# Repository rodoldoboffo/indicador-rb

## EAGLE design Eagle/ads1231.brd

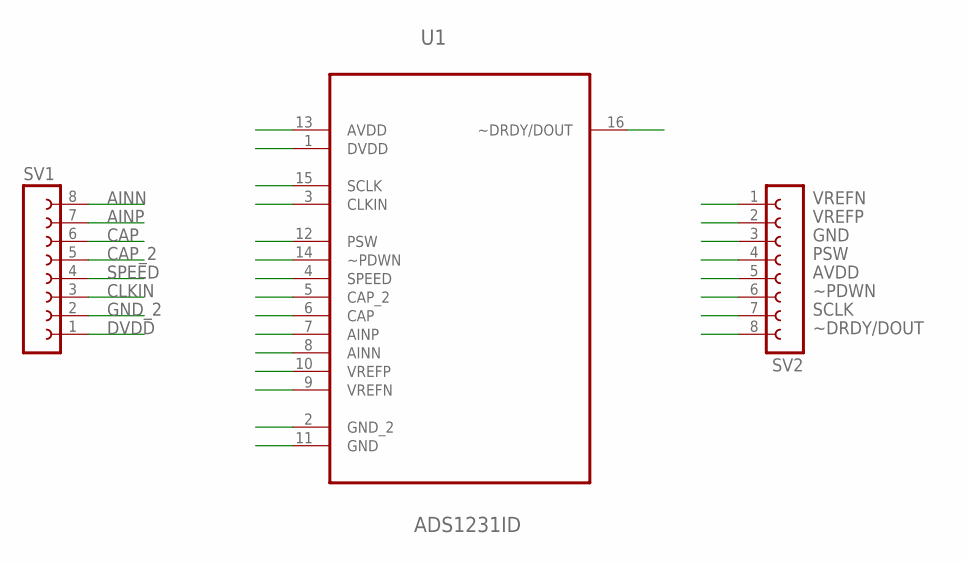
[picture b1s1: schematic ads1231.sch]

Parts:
SV1, SV2: FE08-1; FE08
U1: ADS1231ID; SOIC127P600X175-16N

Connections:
AINN: SV1.8, U1.8 (AINN)
AINP: SV1.7, U1.7 (AINP)
AVDD: SV2.5, U1.13 (AVDD)
CAP: SV1.6, U1.6 (CAP)
CAP_2: SV1.5, U1.5 (CAP_2)
CLKIN: SV1.3, U1.3 (CLKIN)
DVDD: SV1.1, U1.1 (DVDD)
GND: SV2.3, U1.11 (GND)
GND_2: SV1.2, U1.2 (GND_2)
PSW: SV2.4, U1.12 (PSW)
SCLK: SV2.7, U1.15 (SCLK)
SPEED: SV1.4, U1.4 (SPEED)
VREFN: SV2.1, U1.9 (VREFN)
VREFP: SV2.2, U1.10 (VREFP)
~DRDY/DOUT: SV2.8, U1.16 (~DRDY/DOUT)
~PDWN: SV2.6, U1.14 (~PDWN)

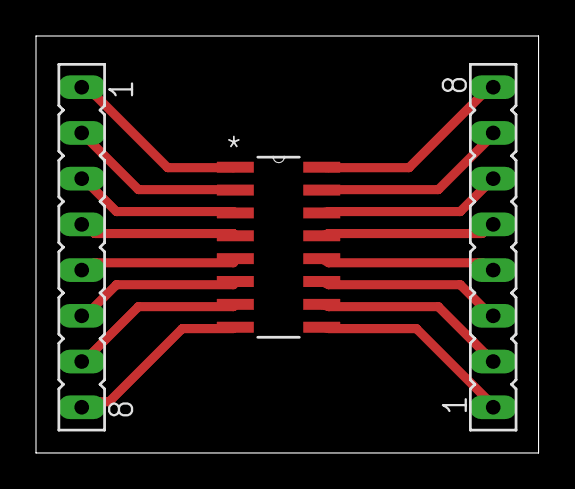
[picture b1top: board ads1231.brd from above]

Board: 2 copper layers, 27.9 x 23.2 mm, 3 parts (0 on the bottom side), 16 nets.

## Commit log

2017-09-09 Grande Commit Inicial
    Esse commit contém todo o projeto até então. Inclui documentos (datasheets), todo código fonte e UI.
2017-09-10 Força de pico
    - Exibição da força/tensão de pico na tela principal
    - Botão para limpar a força/tensão de pico
    - Alteração no layout da tela principal
2017-09-26 Temperature and Clock
    Implementing DS3231 interface. Reading Temperature and Time from DS3231 IC.
2018-06-24 Commitao :(
2018-06-24 COnfiguracao de ferramenta externa AVRDude para Atmel Studio
2018-06-25 Processamento de mensagens através do BLE
2018-06-26 Teste de loop principal. Comandos start e stop para BLE
2018-07-03 Aquisicao Automatica
2018-08-30 Adicionando comandos para operacao com rele
2019-02-17 Adicao de explicacao de como configurar os fusiveis do ATMega328p Adicao de configuracao do programa Extreme Burner
2019-02-18 Limpando funcoes inutilizadas após a inclusao do Bluetooth
2019-02-20 Habilitando relay
2019-02-20 Adicionando esquema de LED SMD Adicionando projeto desenho técnico da placa versao 2.0
2019-02-20 Corrigindo relay AUmentando velocidade da coleta para 80 SPS
2019-02-20 Ajustando local das interrupcoes do Bluetooth
2019-02-20 Removendo arquivos compilados do repositorio
2019-03-04 Limpar o buffer do Bluetooth parece tornar as coisas mais estáveis, com relação a travamentos de leitura.
2019-03-08 Removendo arquivos do git
2019-03-09 Desprezando sempre a primeira leitura do AD, pois ela pode ser sobrescrita; Criando métodos para iniciar e terminar um bloco atomico com relacao a interrupcao de BLE
2019-03-10 Adicionando funcionalidade para se obter o estado do indicador
2019-03-12 Adicionando quebras de linhas para facilitar debuging através do monitor serial
2019-03-13 Ajustando intervalo do loop principal, para ser razoavelmente menor que o intervalo das coletas do app android
2019-03-13 Usando biblioteca de bloco atomico, sugerido pelo AVR
2019-03-14 Removendo delay
2019-03-16 Diminuindo delay do loop principal; Corrigindo gerenciamento do buffer circular do BLE, agora quando o buffer está cheio, movemos o ponteiro para a primeira posicao juntamente com o ponteiro para ult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
2019-03-16 Processamento de comando só ocorre quando é recebido caractere separador de comando
